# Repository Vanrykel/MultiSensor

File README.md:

# MultiSensor

MultiSensor shield for the psoc4 pioneer kit that is also arduino compatible.
- The document folder contains the paper and 'plan van aanpak' for this project. The latter document checks the parts of the project that were finished, which is useful for finding which component 
needs further researching.
- The hardware folder contains the eagle files.
- The software folder contains the software code in seperate folders according to the component of the shield and an order list. The order list contains fragile components that were double ordered called SAFE and an component list for a minimum price value calles FIXED.

[Shield](Shield.jpg)

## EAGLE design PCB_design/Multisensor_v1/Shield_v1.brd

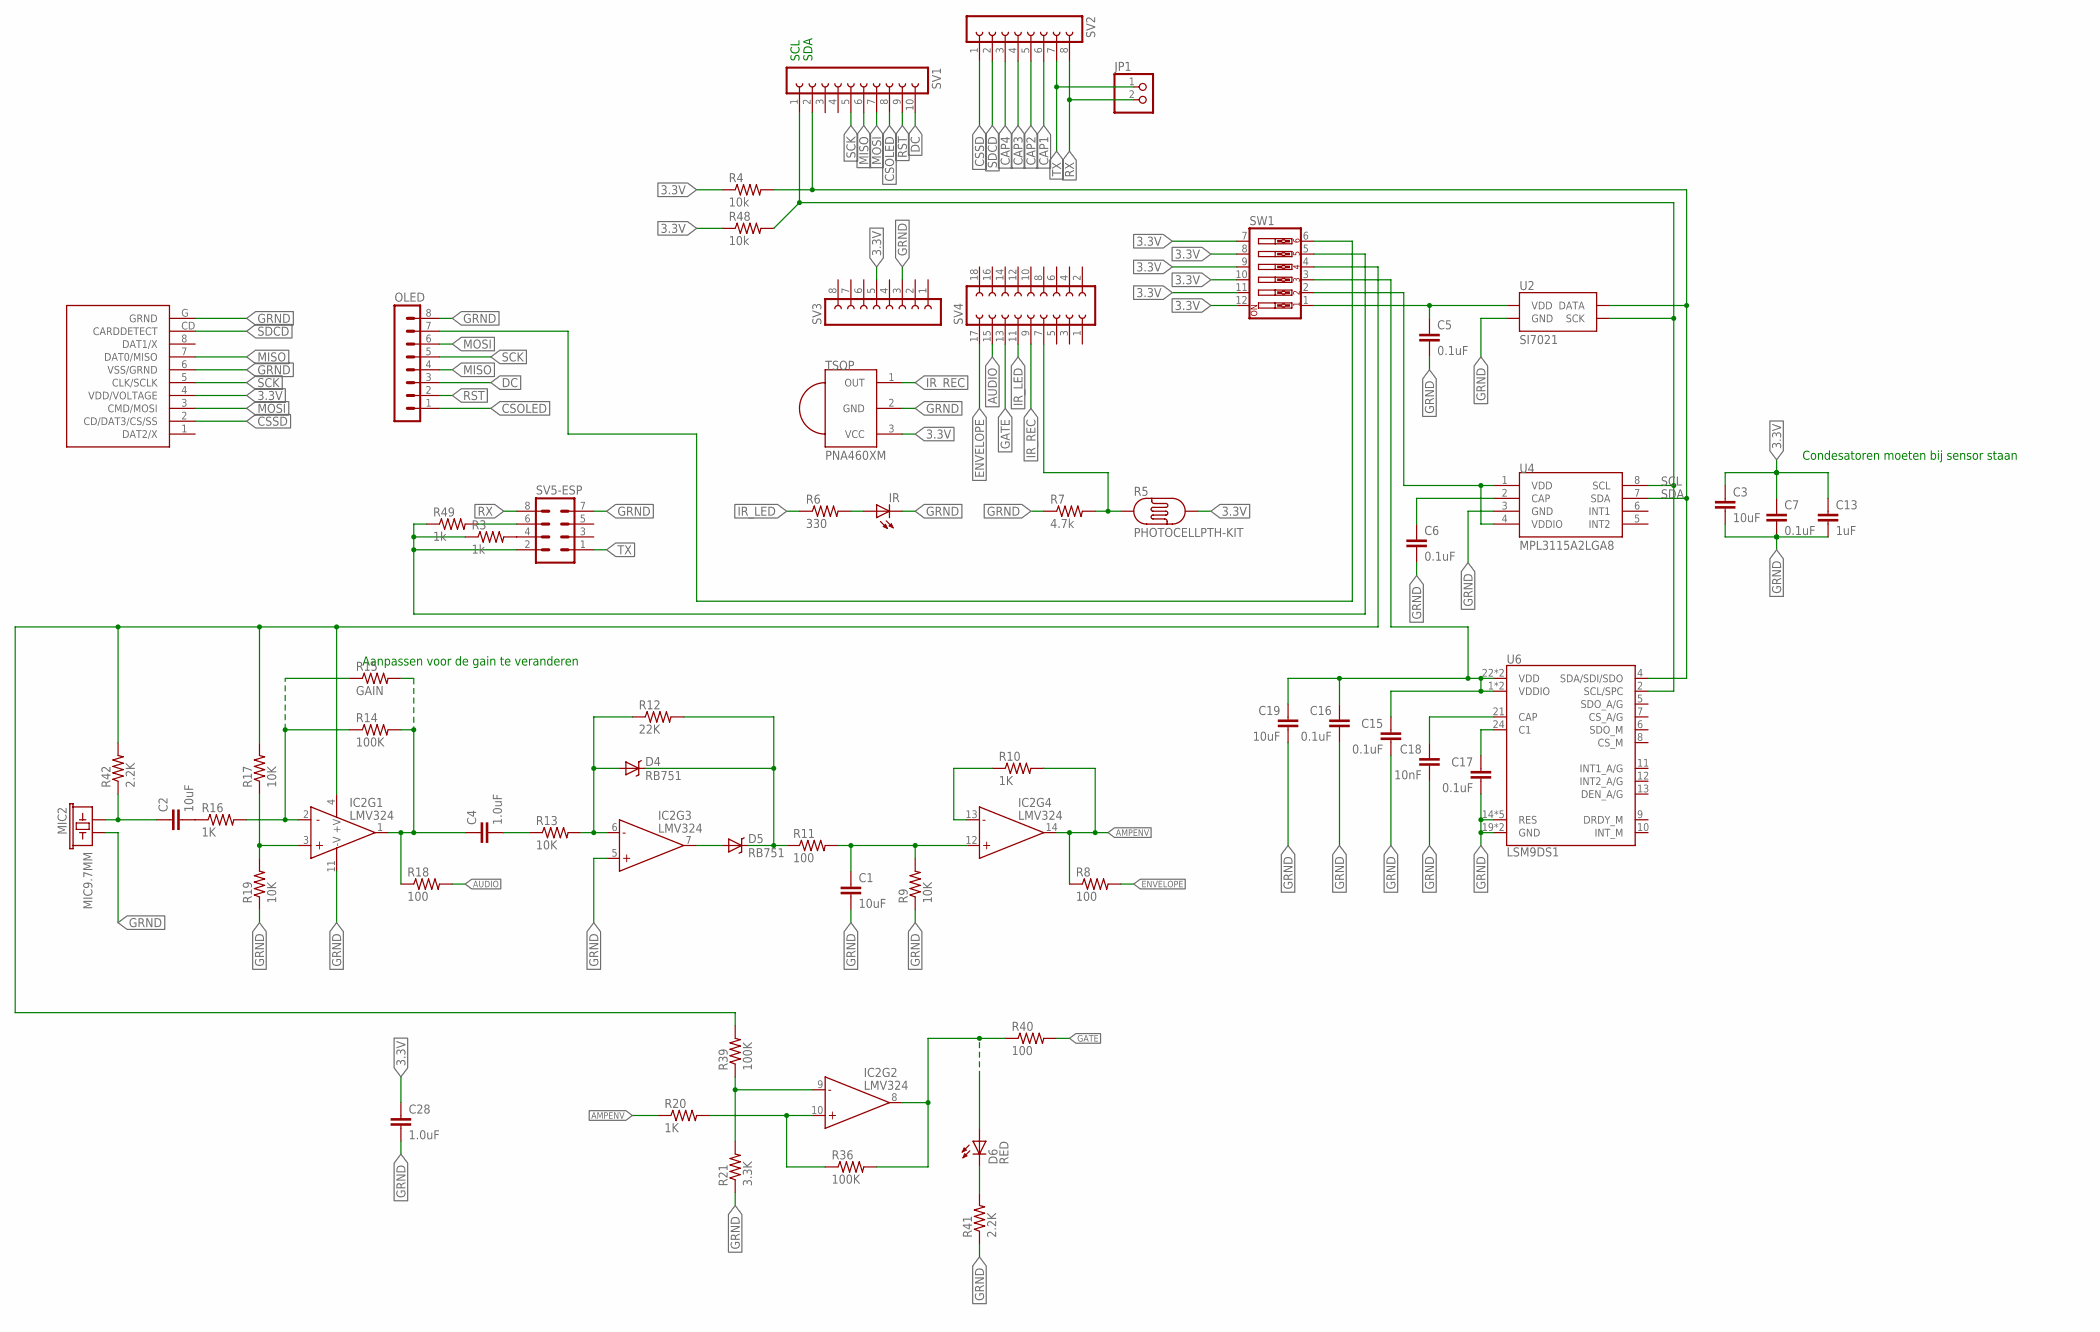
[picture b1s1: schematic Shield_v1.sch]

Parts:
C1, C2, C3, C19: 10uF; C1206
C4, C28: 1.0uF; C1206
C5, C6, C7, C15, C16, C17: 0.1uF; C1206
C13: 1uF; C1206
C18: 10nF; C1206
D4, D5: RB751; SOD-523
D6: RED; LED3MM
IC2: LMV324; SO014
IR: LED5MM
JP1: PINHD-1X2; 1X02
MIC2: MIC9.7MM; MIC-9.7MM
OLED: MA08-1
R3, R49: 1k; R1206
R4, R48: 10k; R1206
R5: PHOTOCELLPTH-KIT; PHOTOCELL-KIT
R6: 330; R1206
R7: 4.7k; R1206
R8, R11, R18, R40: 100; R1206
R9, R13, R17, R19: 10K; R1206
R10, R16, R20: 1K; R1206
R12: 22K; R1206
R14, R36, R39: 100K; R1206
R15: GAIN; R1206
R21: 3.3K; R1206
R41, R42: 2.2K; R1206
SV1: FE10-1; FE10
SV2, SV3: FE08-1; FE08
SV4: FE09-2
SV5-ESP: MA04-2
SW1: SW_DIP-6; EDG-06
TSOP: PNA460XM
U2: SI7021
U4: MPL3115A2LGA8; LGA8
U6: LSM9DS1; LGA24-8X4
U$1: SDCARD; SD_CARD

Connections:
3.3V: C3.1, C7.1, C13.1, C28.1, R4.1, R5.2, R48.1, SV3.5, SW1.7, SW1.8, SW1.9, SW1.10, SW1.11, SW1.12, TSOP.3 (VCC), U$1.4 (VDD/VOLTAGE)
20: SW1.2, U4.1 (VDD), U4.4 (VDDIO)
21: C15.1, C16.1, C19.1, SW1.3, U6.1 (VDDIO), U6.3 (VDDIO), U6.22 (VDD), U6.23 (VDD)
23: IC2.4 (+V), R17.2, R39.2, R42.2, SW1.4
24: R3.1, R49.1, SV5-ESP.2, SW1.5
AMPENV: IC2.14 (OUT), R8.1, R10.2, R20.1
AUDIO: R5.1, R7.2, R18.2, SV4.7, SV4.15
C1: C17.1, U6.24 (C1)
CAP1: SV2.6
CAP2: C18.1, SV2.5, U6.21 (CAP)
CAP3: SV2.4
CAP4: SV2.3
CSOLED: OLED.1, SV1.8
CSSD: SV2.1, U$1.2 (CD/DAT3/CS/SS)
DC: OLED.3, SV1.10
ENVELOPE: R8.2, SV4.17
GATE: R40.2, SV4.13
GRND: C1.2, C3.2, C5.2, C6.2, C7.2, C13.2, C15.2, C16.2, C17.2, C18.2, C19.2, C28.2, IC2.5 (+IN), IC2.11 (-V), IR.K (C), MIC2.2, OLED.8, R7.1, R9.1, R19.1, R21.1, R41.1, SV3.3, SV5-ESP.7, TSOP.2 (GND), U2.GND, U4.3 (GND), U6.14 (RES), U6.15 (RES), U6.16 (RES), U6.17 (RES), U6.18 (RES), U6.19 (GND), U6.20 (GND), U$1.6 (VSS/GRND), U$1.G (GRND)
IR_LED: R6.1, SV4.11
IR_REC: SV4.9, TSOP.1 (OUT)
MISO: OLED.4, SV1.6, U$1.7 (DAT0/MISO)
MOSI: OLED.6, SV1.7, U$1.3 (CMD/MOSI)
N$: C4.1, IC2.1 (OUT), R14.2, R15.2, R18.1
unnamed: C6.1, U4.2 (CAP)
unnamed: IR.A, R6.2
unnamed: C2.1, MIC2.1, R42.1
unnamed: R49.2, SV5-ESP.6
unnamed: R3.2, SV5-ESP.4
unnamed: C5.1, SW1.1, U2.VDD
unnamed: OLED.7, SW1.6
unnamed: IC2.3 (+IN), R17.1, R19.2
unnamed: IC2.2 (-IN), R14.1, R15.1, R16.2
unnamed: C2.2, R16.1
unnamed: C4.2, R13.1
unnamed: D4.A, IC2.6 (-IN), R12.1, R13.2
unnamed: D5.A, IC2.7 (OUT)
unnamed: D4.C, D5.C, R11.1, R12.2
unnamed: C1.1, IC2.12 (+IN), R9.2, R11.2
unnamed: IC2.13 (-IN), R10.1
unnamed: IC2.9 (-IN), R21.2, R39.1
unnamed: IC2.10 (+IN), R20.2, R36.1
unnamed: D6.A, IC2.8 (OUT), R36.2, R40.1
unnamed: D6.K (C), R41.2
RST: OLED.2, SV1.9
RX: JP1.2, SV2.8, SV5-ESP.8
SCK: OLED.5, SV1.5, U$1.5 (CLK/SCLK)
SCL: R48.2, SV1.1, U2.SCK, U4.8 (SCL), U6.2 (SCL/SPC)
SDA: R4.2, SV1.2, U2.DATA, U4.7 (SDA), U6.4 (SDA/SDI/SDO)
SDCD: SV2.2, U$1.CD (CARDDETECT)
TX: JP1.1, SV2.7, SV5-ESP.1

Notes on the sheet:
SCL
SDA
Condesatoren moeten bij sensor staan
Aanpassen voor de gain te veranderen

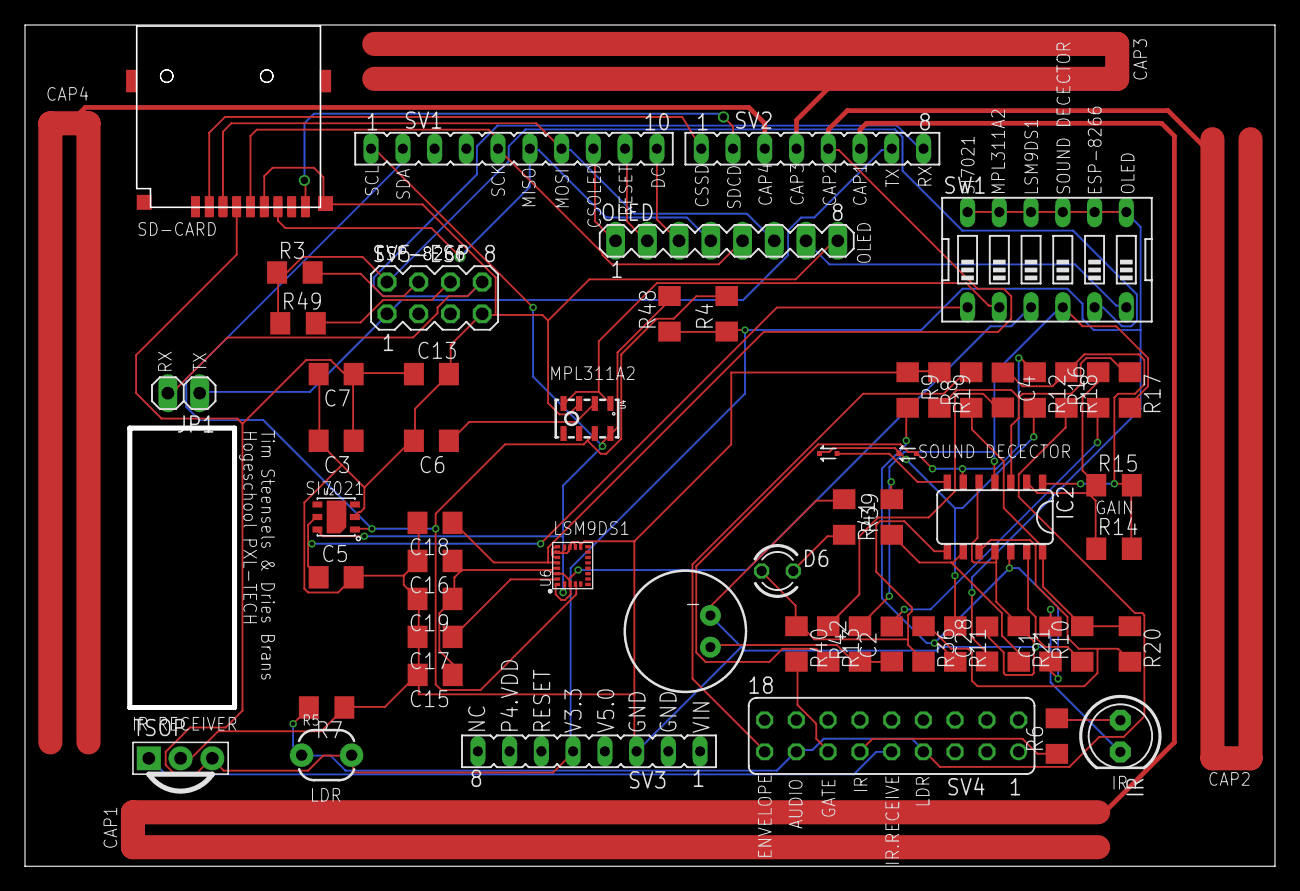
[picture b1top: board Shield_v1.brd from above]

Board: 2 copper layers, 99.6 x 66.9 mm, 59 parts (0 on the bottom side), 47 nets.

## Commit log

2019-03-17 CleanUp
2020-01-24 FixStructure
    Fixing structure and documentation

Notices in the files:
parts and their libraries:
SparkFun-DiscreteSemi: Licensing: CC v3.0 Share-Alike You are welcome to use this library for commercial purposes.
